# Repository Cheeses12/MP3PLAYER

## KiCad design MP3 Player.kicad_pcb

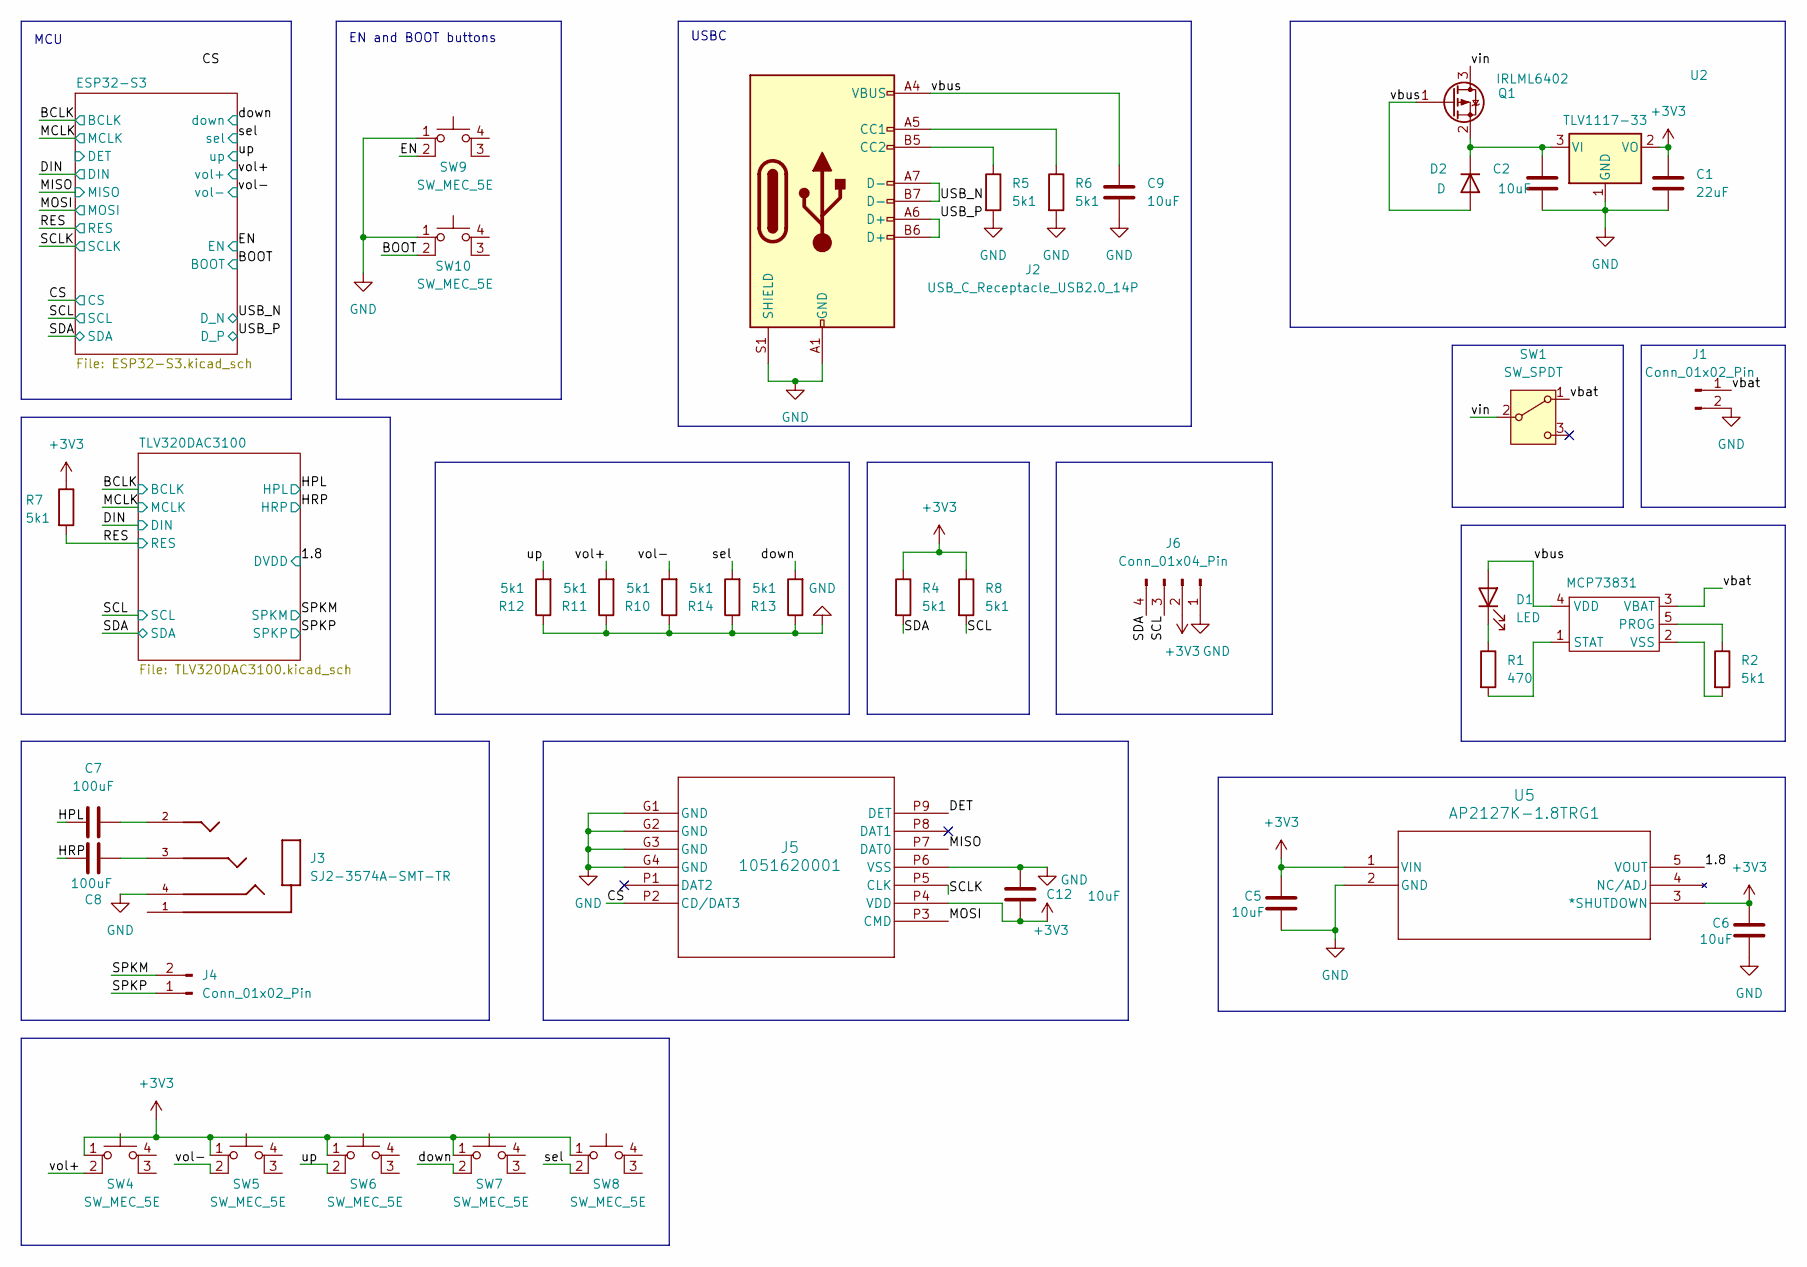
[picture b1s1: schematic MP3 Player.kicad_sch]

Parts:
C1: 22uF; C_0805_2012Metric
C2, C5, C6, C9, C12: 10uF; C_0805_2012Metric
C7, C8: 100uF; C_0805_2012Metric
D1: LED; LED_0603_1608Metric_Pad1.05x0.95mm_HandSolder
D2: D; D_0805_2012Metric
J1: Conn_01x02_Pin; PinHeader_1x02_P2.54mm_Vertical
J2: USB_C_Receptacle_USB2.0_14P; USB_C_Receptacle_GCT_USB4105-xx-A_16P_TopMnt_Horizontal
J3: SJ2-3574A-SMT-TR; 35RASMT4BHNTRX_SWC; PARTREV 1.05
J4: Conn_01x02_Pin; PinHeader_1x02_P1.00mm_Vertical
J5: 1051620001; 105162-0001_MOL
J6: Conn_01x04_Pin; PinHeader_1x04_P2.54mm_Vertical
MCP73831: SOT-23-5_AP2127K_DIO
Q1: IRLML6402; SOT-23
R1: 470; R_0805_2012Metric
R2, R4, R5, R6, R7, R8, R10, R11, R12, R13, R14: 5k1; R_0805_2012Metric
SW1: SW_SPDT; SW_Slide_SPDT_Straight_CK_OS102011MS2Q
SW4, SW5, SW6, SW7, SW8, SW9, SW10: SW_MEC_5E; Panasonic_EVQPUK_EVQPUB
U2: TLV1117-33; DCY0004A_L
U5: AP2127K-1.8TRG1; SOT-23-5_AP2127K_DIO

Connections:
+3V3: C1.1, C5.1, C6.1, C12.2, J5.P4 (VDD), J6.2, R4.1, R7.1, R8.1, SW4.1, SW5.1, SW6.1, SW7.1, SW8.1, U2.2 (VO), U5.1 (VIN), U5.3 (*SHUTDOWN); also elsewhere on the board
/1.8: U5.5 (VOUT); also elsewhere on the board
/BOOT: SW10.2; also elsewhere on the board
/CS: J5.P2 (CD/DAT3); also elsewhere on the board
/DET: J5.P9 (DET)
/EN: SW9.2; also elsewhere on the board
/HPL: C7.2; also elsewhere on the board
/HRP: C8.2; also elsewhere on the board
/MISO: J5.P7 (DAT0); also elsewhere on the board
/MOSI: J5.P3 (CMD); also elsewhere on the board
/RES: R7.2; also elsewhere on the board
/SCL: J6.3, R8.2; also elsewhere on the board
/SCLK: J5.P5 (CLK); also elsewhere on the board
/SDA: J6.4, R4.2; also elsewhere on the board
/SPKM: J4.2; also elsewhere on the board
/SPKP: J4.1; also elsewhere on the board
/USB_N: J2.A7 (D-), J2.B7 (D-); also elsewhere on the board
/USB_P: J2.A6 (D+), J2.B6 (D+); also elsewhere on the board
/down: R13.2, SW7.2; also elsewhere on the board
/sel: R14.2, SW8.2; also elsewhere on the board
/up: R12.2, SW6.2; also elsewhere on the board
/vbat: J1.1, MCP73831.3 (VBAT), SW1.1 (A)
/vbus: C9.1, D1.2 (A), D2.2 (A), J2.A4 (VBUS), J2.A9 (VBUS), J2.B4 (VBUS), J2.B9 (VBUS), MCP73831.4 (VDD), Q1.1 (G)
/vin: Q1.3 (D), SW1.2 (B)
/vol+: R11.2, SW4.2; also elsewhere on the board
/vol-: R10.2, SW5.2; also elsewhere on the board
GND: C1.2, C2.2, C5.2, C6.2, C9.2, C12.1, J1.2, J2.A1 (GND), J2.A12 (GND), J2.B1 (GND), J2.B12 (GND), J2.S1 (SHIELD), J3.4, J5.G1 (GND), J5.G2 (GND), J5.G3 (GND), J5.G4 (GND), J5.P6 (VSS), J6.1, R5.2, R6.2, R10.1, R11.1, R12.1, R13.1, R14.1, SW9.1, SW10.1, U2.1 (GND), U5.2 (GND); also elsewhere on the board
unnamed: C7.1, J3.2
unnamed: C8.1, J3.3
unnamed: D1.1 (K), R1.1
unnamed: C2.1, D2.1 (K), Q1.2 (S), U2.3 (VI)
unnamed: J2.A5 (CC1), R6.1
unnamed: J2.B5 (CC2), R5.1
unnamed: MCP73831.5 (PROG), R2.1
unnamed: MCP73831.1 (STAT), R1.2
unnamed: MCP73831.2 (VSS), R2.2

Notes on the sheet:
USBC
EN and BOOT buttons
MCU

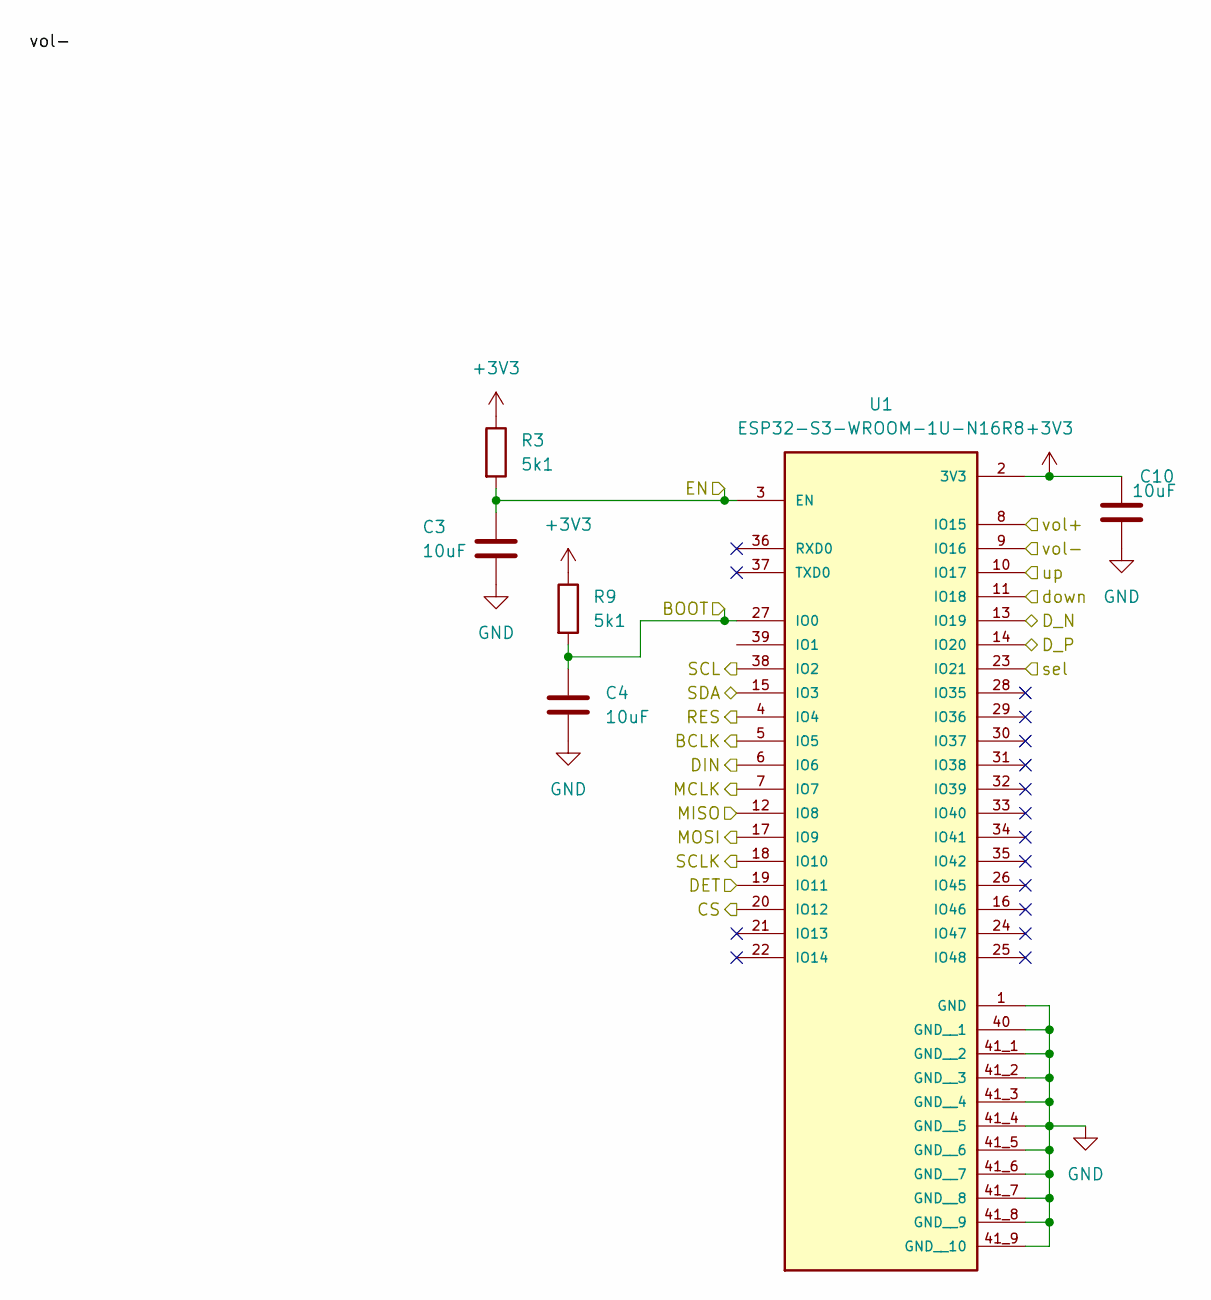
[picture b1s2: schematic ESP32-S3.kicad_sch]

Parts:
C3, C4, C10: 10uF; C_0805_2012Metric
R3, R9: 5k1; R_0805_2012Metric
U1: ESP32-S3-WROOM-1U-N16R8; ESP32-S3-WROOM-1U; PARTREV v1.1

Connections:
+3V3: C10.1, R3.1, R9.1, U1.2 (3V3); also elsewhere on the board
/BCLK: U1.5 (IO5); also elsewhere on the board
/BOOT: C4.1, R9.2, U1.27 (IO0); also elsewhere on the board
/CS: U1.20 (IO12); also elsewhere on the board
/DIN: U1.6 (IO6); also elsewhere on the board
/EN: C3.1, R3.2, U1.3 (EN); also elsewhere on the board
/ESP32-S3/DET: U1.19 (IO11)
/MCLK: U1.7 (IO7); also elsewhere on the board
/MISO: U1.12 (IO8); also elsewhere on the board
/MOSI: U1.17 (IO9); also elsewhere on the board
/RES: U1.4 (IO4); also elsewhere on the board
/SCL: U1.38 (IO2); also elsewhere on the board
/SCLK: U1.18 (IO10); also elsewhere on the board
/SDA: U1.15 (IO3); also elsewhere on the board
/USB_N: U1.13 (IO19); also elsewhere on the board
/USB_P: U1.14 (IO20); also elsewhere on the board
/down: U1.11 (IO18); also elsewhere on the board
/sel: U1.23 (IO21); also elsewhere on the board
/up: U1.10 (IO17); also elsewhere on the board
/vol+: U1.8 (IO15); also elsewhere on the board
/vol-: U1.9 (IO16); also elsewhere on the board
GND: C3.2, C4.2, C10.2, U1.1 (GND), U1.40 (GND__1), U1.41_1 (GND__2), U1.41_2 (GND__3), U1.41_3 (GND__4), U1.41_4 (GND__5), U1.41_5 (GND__6), U1.41_6 (GND__7), U1.41_7 (GND__8), U1.41_8 (GND__9), U1.41_9 (GND__10); also elsewhere on the board

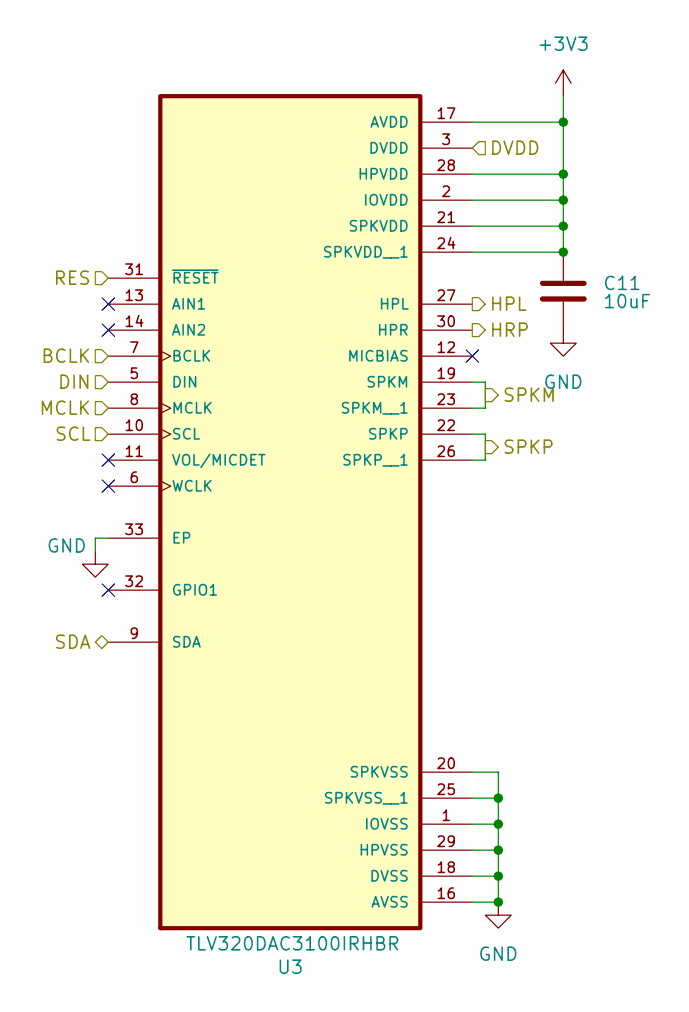
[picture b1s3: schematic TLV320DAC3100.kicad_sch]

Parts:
C11: 10uF; C_0805_2012Metric
U3: TLV320DAC3100IRHBR; IC_ADS125H01IRHBT

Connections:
+3V3: C11.1, U3.2 (IOVDD), U3.17 (AVDD), U3.21 (SPKVDD), U3.24 (SPKVDD__1), U3.28 (HPVDD); also elsewhere on the board
/1.8: U3.3 (DVDD); also elsewhere on the board
/BCLK: U3.7 (BCLK); also elsewhere on the board
/DIN: U3.5 (DIN); also elsewhere on the board
/HPL: U3.27 (HPL); also elsewhere on the board
/HRP: U3.30 (HPR); also elsewhere on the board
/MCLK: U3.8 (MCLK); also elsewhere on the board
/RES: U3.31 (~RESET); also elsewhere on the board
/SCL: U3.10 (SCL); also elsewhere on the board
/SDA: U3.9 (SDA); also elsewhere on the board
/SPKM: U3.19 (SPKM), U3.23 (SPKM__1); also elsewhere on the board
/SPKP: U3.22 (SPKP), U3.26 (SPKP__1); also elsewhere on the board
GND: C11.2, U3.1 (IOVSS), U3.16 (AVSS), U3.18 (DVSS), U3.20 (SPKVSS), U3.25 (SPKVSS__1), U3.29 (HPVSS), U3.33 (EP); also elsewhere on the board

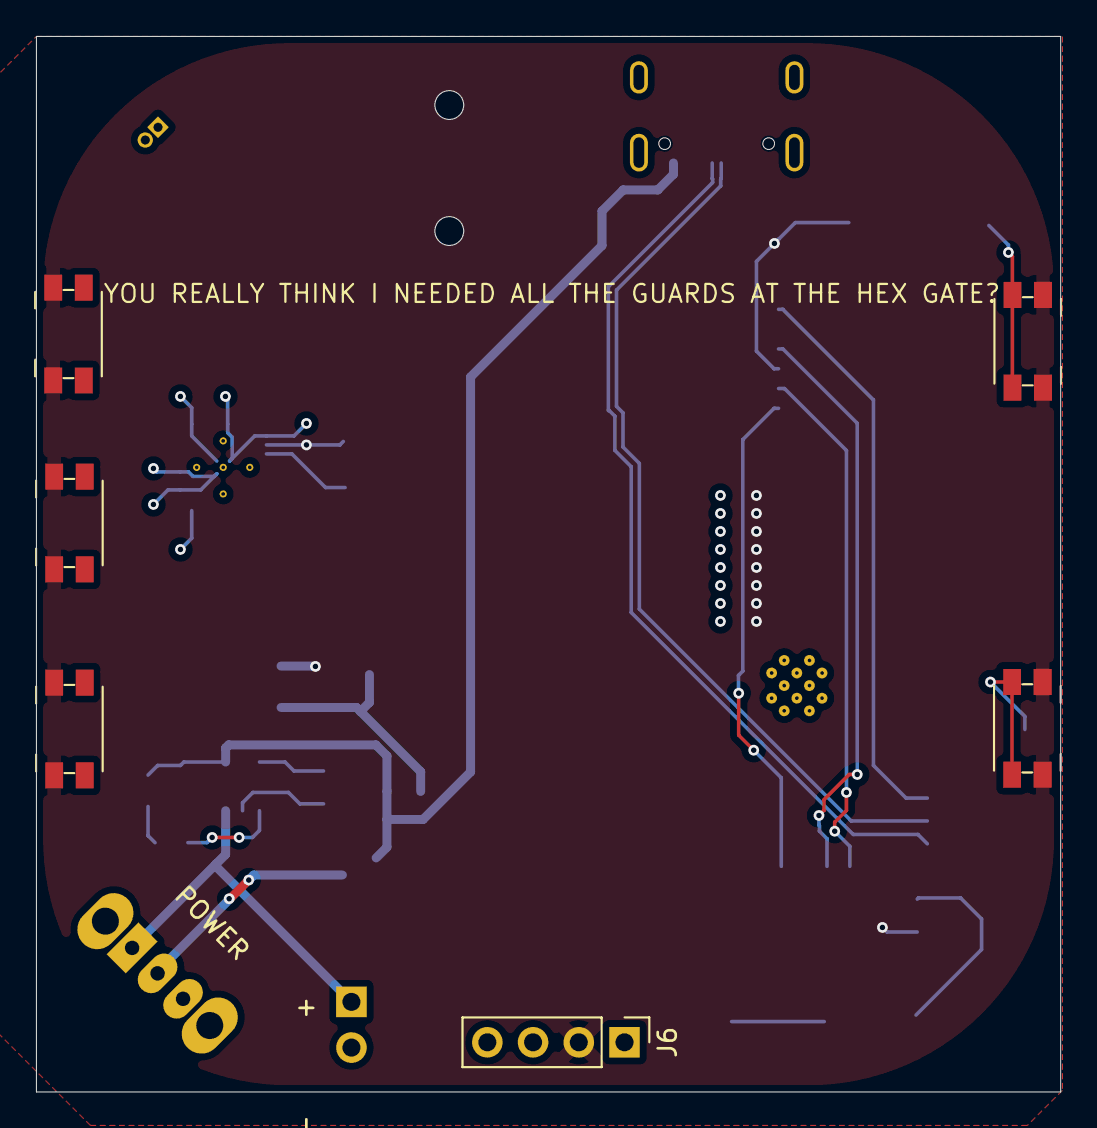
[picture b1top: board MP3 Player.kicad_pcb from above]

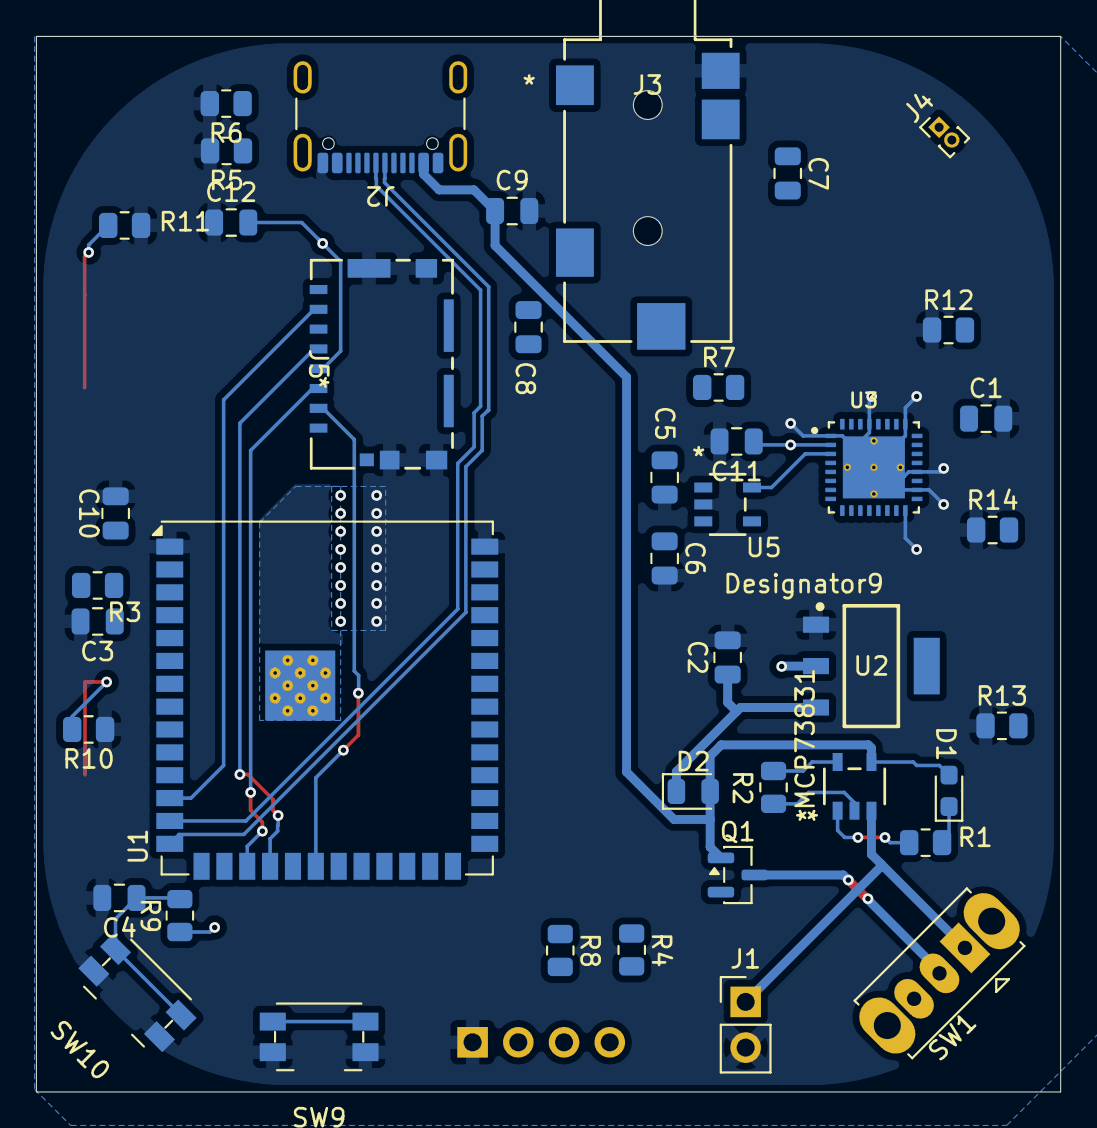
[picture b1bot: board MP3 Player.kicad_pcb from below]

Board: 2 copper layers, 56.9 x 58.6 mm, 48 parts (42 on the bottom side), 38 nets.

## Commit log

2026-04-13 First commit for board
2026-04-15 Cleaned up the schematic
2026-04-22 Cleaned up schematic
2026-04-22 updated board design
2026-05-13 updated board design to fit altoid tin
